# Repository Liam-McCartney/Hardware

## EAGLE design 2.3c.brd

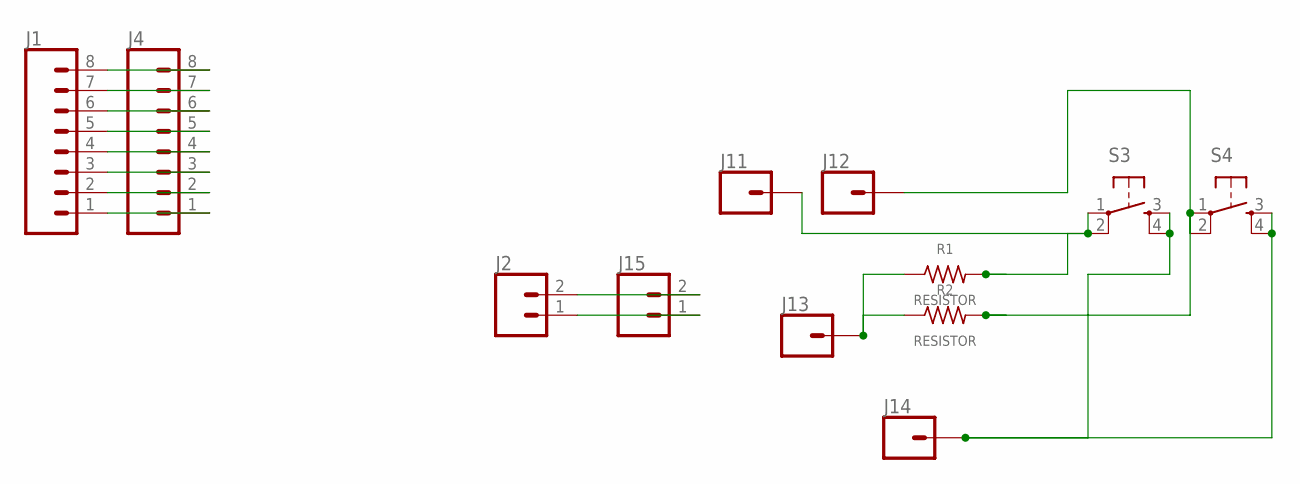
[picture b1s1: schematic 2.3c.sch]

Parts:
J1, J4: CONN_08"; 1X08
J2, J15: CONN_02; 1X02
J11, J12, J13, J14: CONN_01; 1X01
R1, R2: RESISTOR; 0207/10
S3, S4: TAC_SWITCHPTH; TACTILE-PTH

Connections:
unnamed: J11.1, R1.2, S3.1, S3.2
unnamed: J13.1, R1.1, R2.1
unnamed: J2.2, J15.2
unnamed: J2.1, J15.1
unnamed: J1.1, J4.1
unnamed: J1.2, J4.2
unnamed: J1.3, J4.3
unnamed: J1.4, J4.4
unnamed: J1.5, J4.5
unnamed: J1.6, J4.6
unnamed: J1.7, J4.7
unnamed: J1.8, J4.8
unnamed: J12.1, R2.2, S4.1, S4.2
unnamed: J14.1, S3.3, S3.4, S4.3, S4.4

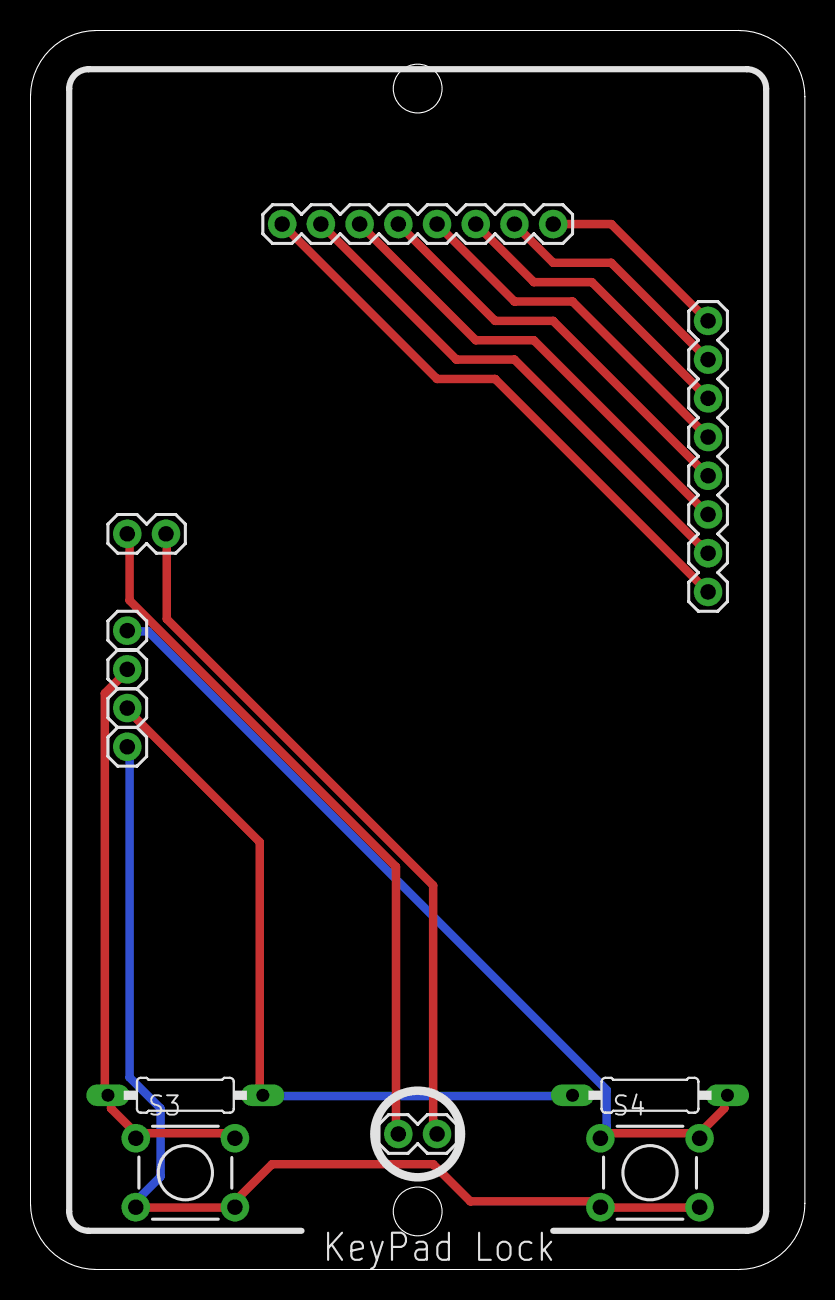
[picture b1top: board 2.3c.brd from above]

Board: 2 copper layers, 50.8 x 81.3 mm, 12 parts (0 on the bottom side), 14 nets.

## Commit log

2023-03-10 Create Desmos Graph
2023-03-10 Delete Medium ISP The WireFrame Rotator.ino
    I'm dumb i used int instead of uint8_t
2023-04-01 Create KeyPad Lock (2.3c)
2023-05-07 Create null
2024-04-13 Create Desmos Simulation

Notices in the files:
parts and their libraries:
SparkFun-Connectors: Licensing: Creative Commons ShareAlike 4.0 International - https://creativecommons.org/licenses/by-sa/4.0
